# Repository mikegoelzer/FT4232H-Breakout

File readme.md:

# FT4232H Breakout Board

Breakout board for the FT4232H to support SPI flash programming and JTAG, as well as two UARTs.

# Contents

 - [`ft4232h-bob-v0/`](ft4232h-bob-v0/) - Rev 0 of hardware
 - [`mfgr/`](mfgr/) - Files used to initial the EEPROM in a newly built device. See [`mfgr/README.md`](mfgr/README.md)
 - [`ft4232h-bob-v0/docs/`](ft4232h-bob-v0/docs/) - Documentation:
   - [`ft4232h-bob-v0/docs/Improvements.md`](ft4232h-bob-v0/docs/Improvements.md) - Improvements to make to for next revision of board

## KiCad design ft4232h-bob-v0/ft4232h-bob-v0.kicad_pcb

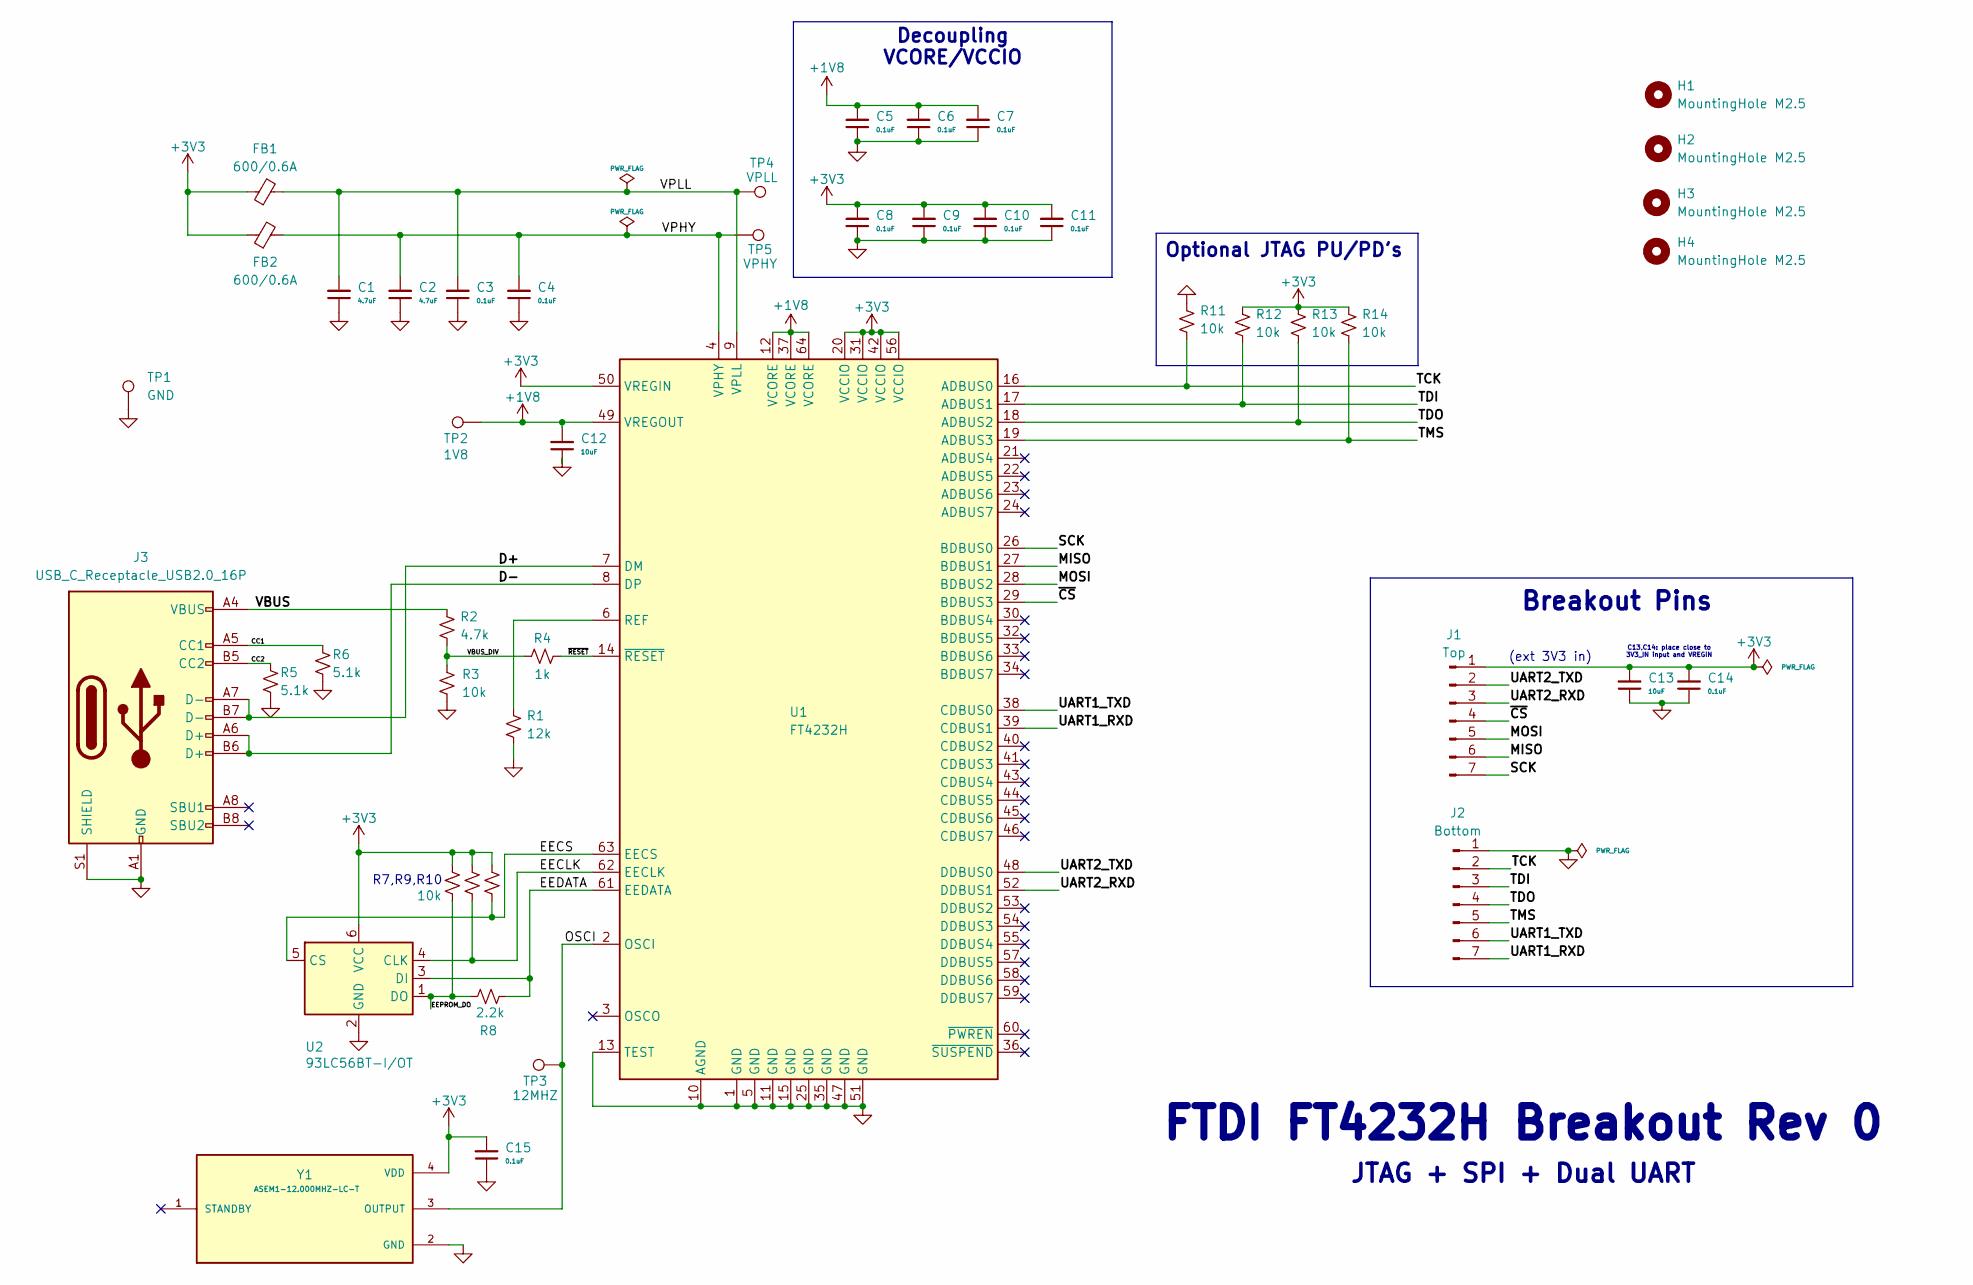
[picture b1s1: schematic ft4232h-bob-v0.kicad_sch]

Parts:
C1, C2: 4.7uF; C_0805_2012Metric_Pad1.18x1.45mm_HandSolder
C3, C4, C5, C6, C7, C8, C9, C10, C11, C14, C15: 0.1uF; C_0805_2012Metric_Pad1.18x1.45mm_HandSolder
C12, C13: 10uF; C_0805_2012Metric_Pad1.18x1.45mm_HandSolder
FB1, FB2: 600/0.6A; L_0805_2012Metric_Pad1.15x1.40mm_HandSolder
H1, H2, H3, H4: MountingHole M2.5; MountingHole_2.7mm_M2.5_ISO7380
J1: Top; PinHeader_1x07_P2.54mm_Vertical-Circular-Pads
J2: Bottom; PinHeader_1x07_P2.54mm_Vertical-Circular-Pads
J3: USB_C_Receptacle_USB2.0_16P; USB_C_Receptacle_GCT_USB4085
R1: 12k; R_0805_2012Metric_Pad1.15x1.40mm_HandSolder
R2: 4.7k; R_0805_2012Metric_Pad1.15x1.40mm_HandSolder
R3, R7, R9, R10, R11, R12, R13, R14: 10k; R_0805_2012Metric_Pad1.15x1.40mm_HandSolder
R4: 1k; R_0805_2012Metric_Pad1.15x1.40mm_HandSolder
R5, R6: 5.1k; R_0805_2012Metric_Pad1.15x1.40mm_HandSolder
R8: 2.2k; R_0805_2012Metric_Pad1.15x1.40mm_HandSolder
TP1: GND; TestPoint_Pad_2.0x2.0mm
TP2: 1V8; TestPoint_Pad_2.0x2.0mm
TP3: 12MHZ; TestPoint_Pad_2.0x2.0mm
TP4: VPLL; TestPoint_Pad_2.0x2.0mm
TP5: VPHY; TestPoint_Pad_2.0x2.0mm
U1: FT4232H; LQFP-64_10x10mm_P0.5mm
U2: 93LC56BT-I/OT; SOT-23-6; MPN 93LC56BT-I/OT
Y1: ASEM1-12.000MHZ-LC-T; XTAL_ASEM1-12.000MHZ-LC-T; PARTREV 1.4.2021

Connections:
+1V8: C5.2, C6.2, C7.2, C12.2, TP2.1, U1.12 (VCORE), U1.37 (VCORE), U1.49 (VREGOUT), U1.64 (VCORE)
+3V3: C8.2, C9.2, C10.2, C11.2, C13.2, C14.2, C15.2, FB1.1, FB2.1, J1.1, R7.1, R9.1, R10.1, R12.1, R13.1, R14.1, U1.20 (VCCIO), U1.31 (VCCIO), U1.42 (VCCIO), U1.50 (VREGIN), U1.56 (VCCIO), U2.6 (VCC), Y1.4 (VDD)
/CC1: J3.A5 (CC1), R6.1
/CC2: J3.B5 (CC2), R5.1
/D+: J3.A7 (D-), J3.B7 (D-), U1.7 (DM)
/D-: J3.A6 (D+), J3.B6 (D+), U1.8 (DP)
/EECLK: R9.2, U1.62 (EECLK), U2.4 (CLK)
/EECS: R10.2, U1.63 (EECS), U2.5 (CS)
/EEDATA: R8.2, U1.61 (EEDATA), U2.3 (DI)
/EEPROM_DO: R7.2, R8.1, U2.1 (DO)
/MISO: J1.6, U1.27 (BDBUS1)
/MOSI: J1.5, U1.28 (BDBUS2)
/OSCI: TP3.1, U1.2 (OSCI), Y1.3 (OUTPUT)
/SCK: J1.7, U1.26 (BDBUS0)
/TCK: J2.2, R11.2, U1.16 (ADBUS0)
/TDI: J2.3, R12.2, U1.17 (ADBUS1)
/TDO: J2.4, R13.2, U1.18 (ADBUS2)
/TMS: J2.5, R14.2, U1.19 (ADBUS3)
/UART1_RXD: J2.7, U1.39 (CDBUS1)
/UART1_TXD: J2.6, U1.38 (CDBUS0)
/UART2_RXD: J1.3, U1.52 (DDBUS1)
/UART2_TXD: J1.2, U1.48 (DDBUS0)
/VBUS: J3.A4 (VBUS), J3.A9 (VBUS), J3.B4 (VBUS), J3.B9 (VBUS), R2.1
/VBUS_DIV: R2.2, R3.1, R4.1
/VPHY: C2.2, C4.2, FB2.2, TP5.1, U1.4 (VPHY)
/VPLL: C1.2, C3.2, FB1.2, TP4.1, U1.9 (VPLL)
/~CS: J1.4, U1.29 (BDBUS3)
/~RESET: R4.2, U1.14 (~RESET)
GND: C1.1, C2.1, C3.1, C4.1, C5.1, C6.1, C7.1, C8.1, C9.1, C10.1, C11.1, C12.1, C13.1, C14.1, C15.1, J2.1, J3.A1 (GND), J3.A12 (GND), J3.B1 (GND), J3.B12 (GND), J3.S1 (SHIELD), R1.2, R3.2, R5.2, R6.2, R11.1, TP1.1, U1.1 (GND), U1.5 (GND), U1.10 (AGND), U1.11 (GND), U1.13 (TEST), U1.15 (GND), U1.25 (GND), U1.35 (GND), U1.47 (GND), U1.51 (GND), U2.2 (GND), Y1.2 (GND)
unnamed: R1.1, U1.6 (REF)

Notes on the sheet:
Optional JTAG PU/PD's
Breakout Pins
FTDI FT4232H Breakout Rev 0
Decoupling VCORE/VCCIO
JTAG + SPI + Dual UART
(ext 3V3 in)
C13,C14: place close to 3V3_IN input and VREGIN
R7,R9,R10

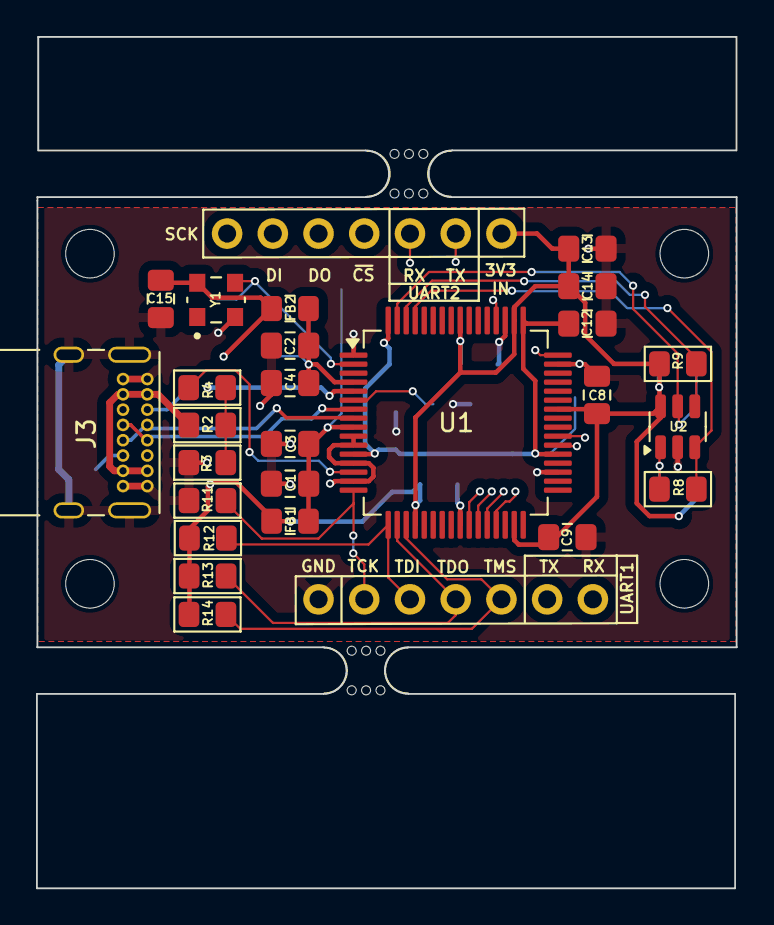
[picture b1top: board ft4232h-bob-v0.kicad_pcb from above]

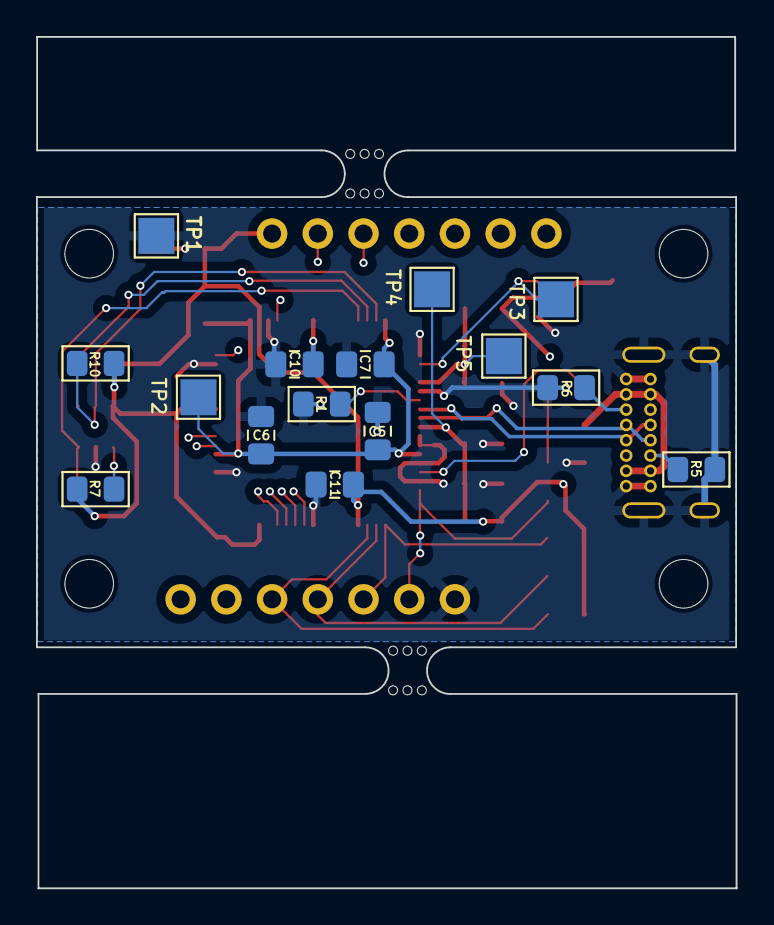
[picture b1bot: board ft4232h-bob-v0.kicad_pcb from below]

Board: 4 copper layers, 38.9 x 47.3 mm, 48 parts (15 on the bottom side), 30 nets.

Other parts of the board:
mouse-bite-2.54mm-slot, mouse-bite-2.54mm-slot#2: VAL**; mouse-bite-2.54mm-slot

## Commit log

2024-09-16 initial commit: v0 hardware + eepromm initialization files
2024-09-16 fix readme
2024-09-16 readme typo fix
2024-09-17 fix empty serial number in ftdiflash -l
2024-12-23 minor edit to spreadsheet
2024-12-30 added schematic note about MISO/MOSI swap needed (see improvements.md)
